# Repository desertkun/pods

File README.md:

# pods

Compact game console on `STM32F103RC6` chip with network module `NRF24L01` and `SH1106` display designed to be made as a pair.

To compile this, you'll need to install the [System Workbench for STM32](http://www.openstm32.org/Downloading%2Bthe%2BSystem%2BWorkbench%2Bfor%2BSTM32%2Binstaller) (requires an account to download).

The `layout` folder contains KiCad project for [schematics](https://user-images.githubusercontent.com/1666014/50406018-09bfe200-07c6-11e9-8298-aad8884d8a90.png).

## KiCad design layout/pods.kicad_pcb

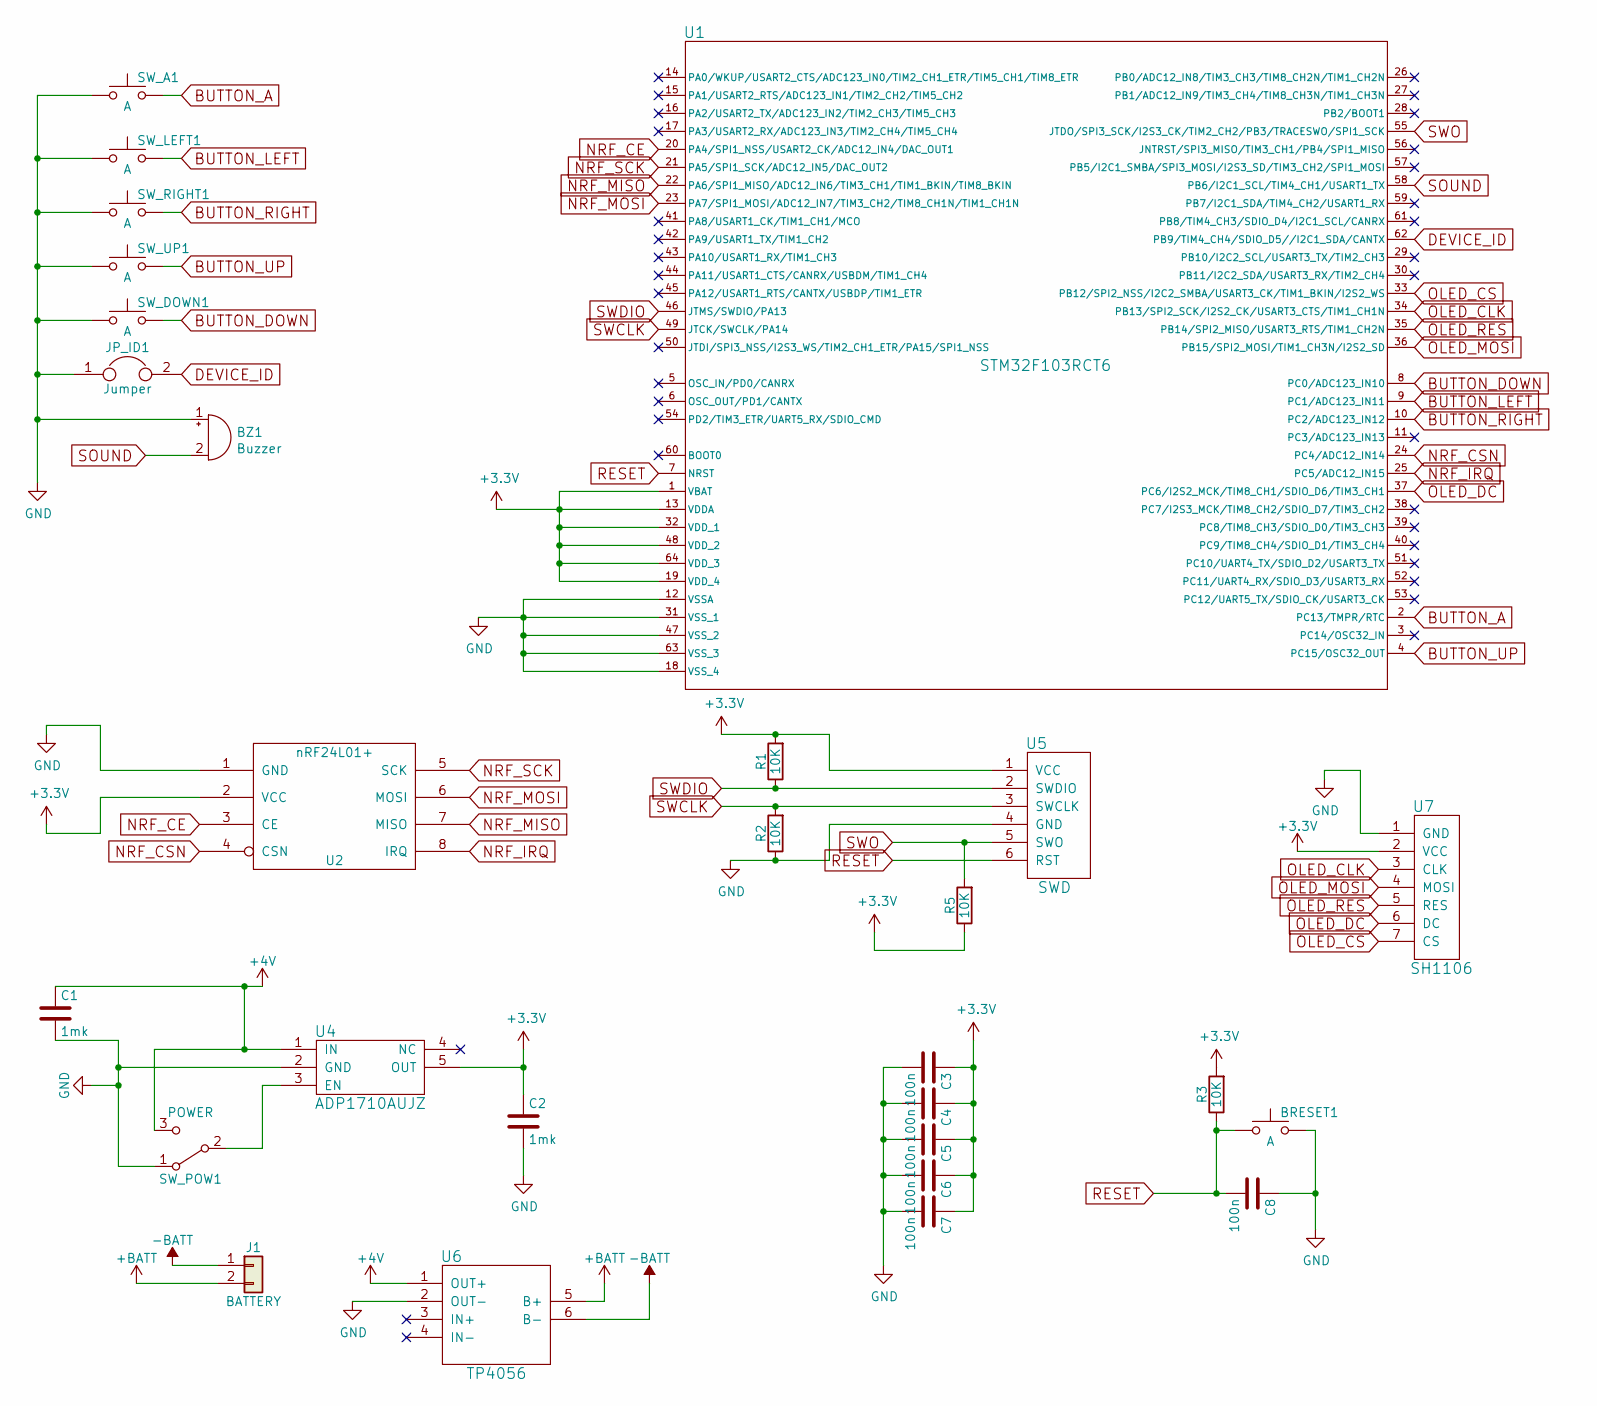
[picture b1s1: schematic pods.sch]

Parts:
BRESET1: A; SW_TH_Tactile_Omron_Fixed
BZ1: Buzzer; SolderWirePad_1x02_P3.81mm_Drill0.8mm
C1, C2: 1mk; C_0805_2012Metric_Pad1.15x1.40mm_HandSolder
C3, C4, C5, C6, C7, C8: 100n; C_0805_2012Metric_Pad1.15x1.40mm_HandSolder
J1: BATTERY; SolderWirePad_1x02_P3.81mm_Drill0.8mm
JP_ID1: Jumper; SolderWirePad_1x02_P3.81mm_Drill0.8mm
R1, R2, R3, R5: 10K; R_0805_2012Metric_Pad1.15x1.40mm_HandSolder
SW_A1: A; SW_TH_Tactile_Omron_Fixed
SW_DOWN1: A; SW_TH_Tactile_Omron_Fixed
SW_LEFT1: A; SW_TH_Tactile_Omron_Fixed
SW_POW1: POWER; SolderWirePad_1x03_P3.175mm_Drill0.8mm
SW_RIGHT1: A; SW_TH_Tactile_Omron_Fixed
SW_UP1: A; SW_TH_Tactile_Omron_Fixed
U1: STM32F103RCT6; LQFP-64_10x10mm_Pitch0.5mm
U2: nRF24L01+; NRF24L01
U4: ADP1710AUJZ; SOT-23-5_HandSoldering
U5: SWD; PinHeader_2x03_P2.54mm_Horizontal
U6: TP4056; tp4056
U7: SH1106; sh1106

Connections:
+3V3: C2.1, C3.1, C4.1, C5.1, C6.1, C7.1, R1.2, R3.2, R5.1, U1.1 (VBAT), U1.13 (VDDA), U1.19 (VDD_4), U1.32 (VDD_1), U1.48 (VDD_2), U1.64 (VDD_3), U2.2 (VCC), U4.5 (OUT), U5.1 (VCC), U7.2 (VCC)
+4V: C1.1, SW_POW1.3 (C), U4.1 (IN), U6.1 (OUT+)
+BATT: J1.2, U6.5 (B+)
-BATT: J1.1, U6.6 (B-)
BUTTON_A: SW_A1.2, U1.2 (PC13/TMPR/RTC)
BUTTON_DOWN: SW_DOWN1.2, U1.8 (PC0/ADC123_IN10)
BUTTON_LEFT: SW_LEFT1.2, U1.9 (PC1/ADC123_IN11)
BUTTON_RIGHT: SW_RIGHT1.2, U1.10 (PC2/ADC123_IN12)
BUTTON_UP: SW_UP1.2, U1.4 (PC15/OSC32_OUT)
DEVICE_ID: JP_ID1.2, U1.62 (PB9/TIM4_CH4/SDIO_D5//I2C1_SDA/CANTX)
GND: BRESET1.2, BZ1.1 (-), C1.2, C2.2, C3.2, C4.2, C5.2, C6.2, C7.2, C8.1, JP_ID1.1, R2.1, SW_A1.1, SW_DOWN1.1, SW_LEFT1.1, SW_POW1.1 (A), SW_RIGHT1.1, SW_UP1.1, U1.12 (VSSA), U1.18 (VSS_4), U1.31 (VSS_1), U1.47 (VSS_2), U1.63 (VSS_3), U2.1 (GND), U4.2 (GND), U5.4 (GND), U6.2 (OUT-), U7.1 (GND)
NRF_CE: U1.20 (PA4/SPI1_NSS/USART2_CK/ADC12_IN4/DAC_OU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), U2.3 (CE)
NRF_CSN: U1.24 (PC4/ADC12_IN14), U2.4 (CSN)
NRF_IRQ: U1.25 (PC5/ADC12_IN15), U2.8 (IRQ)
NRF_MISO: U1.22 (PA6/SPI1_MISO/ADC12_IN6/TIM3_CH1/TIM1_B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), U2.7 (MISO)
NRF_MOSI: U1.23 (PA7/SPI1_MOSI/ADC12_IN7/TIM3_CH2/TIM8_C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), U2.6 (MOSI)
NRF_SCK: U1.21 (PA5/SPI1_SCK/ADC12_IN5/DAC_OUT2), U2.5 (SCK)
unnamed: SW_POW1.2 (B), U4.3 (EN)
OLED_CLK: U1.34 (PB13/SPI2_SCK/I2S2_CK/USART3_CTS/TIM1_C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), U7.3 (CLK)
OLED_CS: U1.33 (PB12/SPI2_NSS/I2C2_SMBA/USART3_CK/TIM1_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), U7.7 (CS)
OLED_DC: U1.37 (PC6/I2S2_MCK/TIM8_CH1/SDIO_D6/TIM3_CH1), U7.6 (DC)
OLED_MOSI: U1.36 (PB15/SPI2_MOSI/TIM1_CH3N/I2S2_SD), U7.4 (MOSI)
OLED_RES: U1.35 (PB14/SPI2_MISO/USART3_RTS/TIM1_CH2N), U7.5 (RES)
RESET: BRESET1.1, C8.2, R3.1, U1.7 (NRST), U5.6 (RST)
SOUND: BZ1.2 (+), U1.58 (PB6/I2C1_SCL/TIM4_CH1/USART1_TX)
SWCLK: R2.2, U1.49 (JTCK/SWCLK/PA14), U5.3 (SWCLK)
SWDIO: R1.1, U1.46 (JTMS/SWDIO/PA13), U5.2 (SWDIO)
SWO: R5.2, U1.55 (JTDO/SPI3_SCK/I2S3_CK/TIM2_CH2/PB3/TRAC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), U5.5 (SWO)

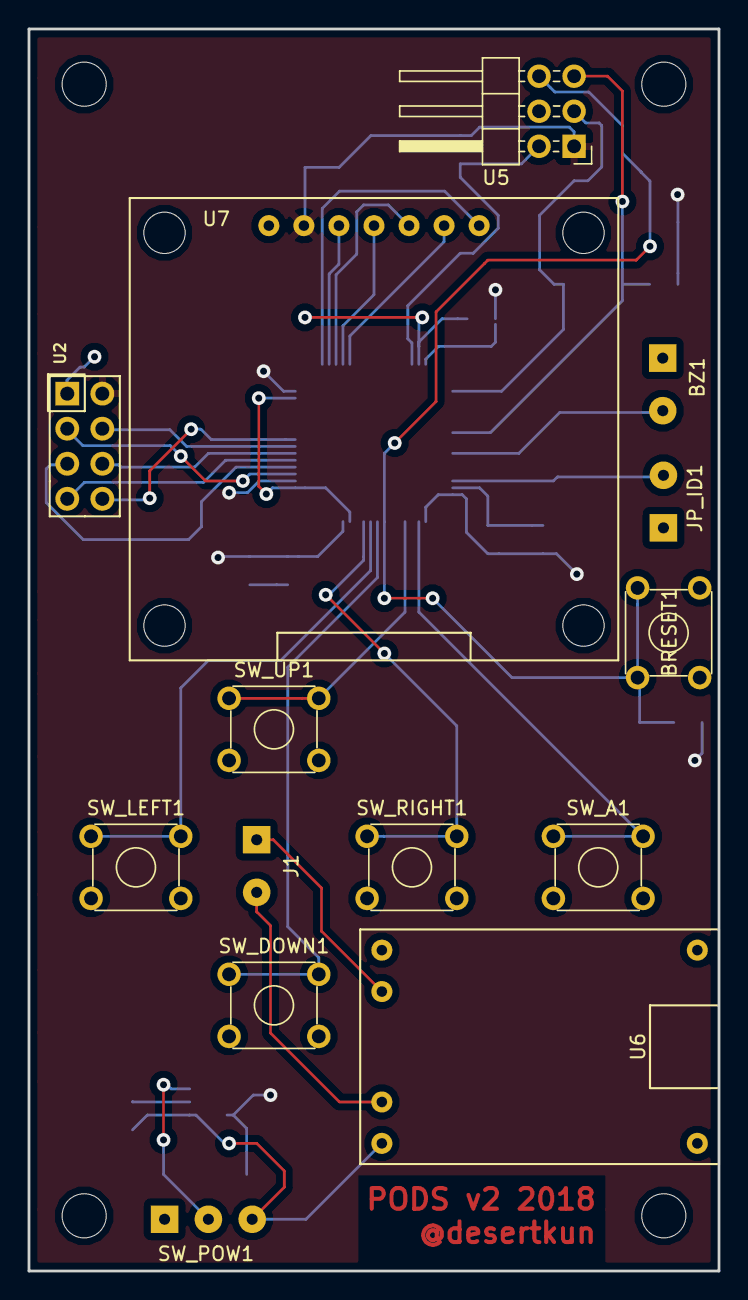
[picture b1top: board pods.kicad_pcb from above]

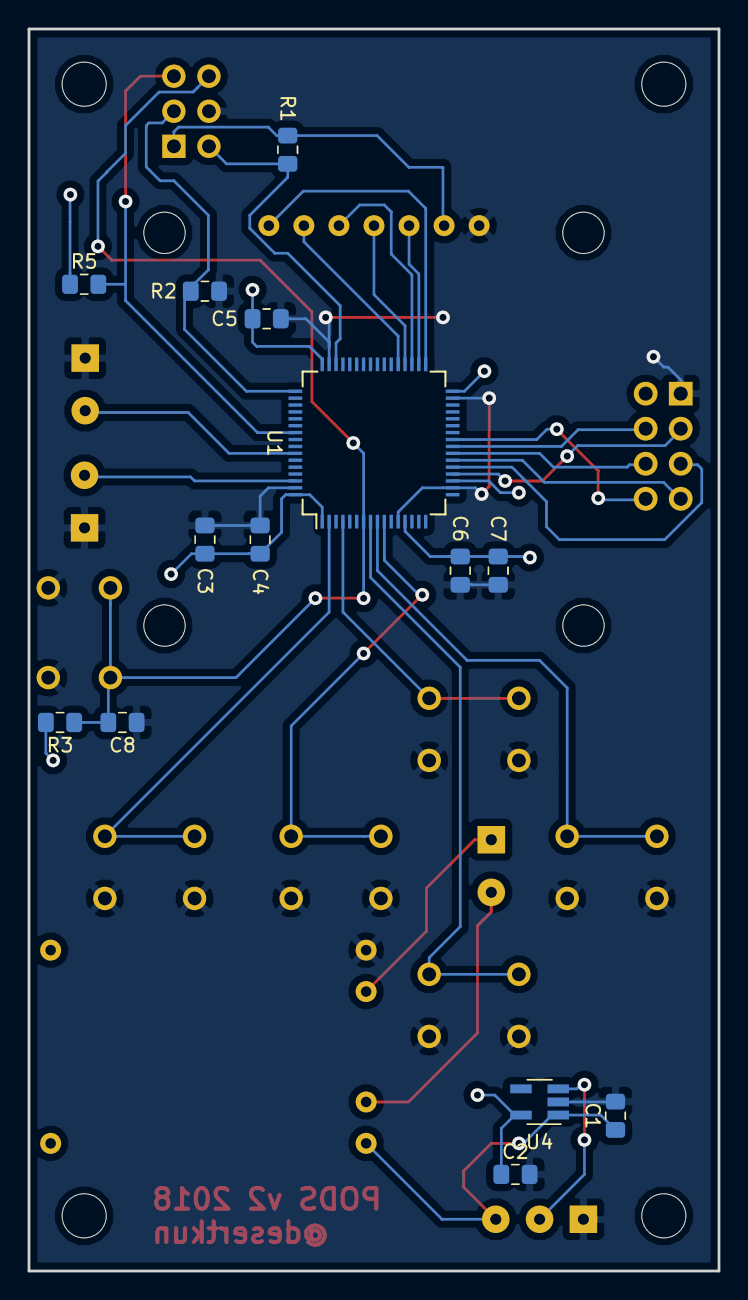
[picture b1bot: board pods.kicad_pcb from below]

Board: 2 copper layers, 50.0 x 90.0 mm, 28 parts (14 on the bottom side), 28 nets.

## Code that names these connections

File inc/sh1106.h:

#ifndef __SH1106_H
#define __SH1106_H

#include "stm32f1xx_hal.h"
#include "main.h"

// SH1106 display connection:
//   PB8 --> CS
//   PB9 --> RES
//   PC0 --> DC
//   PA5 --> D0 (SCK)
//   PA7 --> D1 (MOSI)


// Use bit-banding to draw pixel
//   0 - use logic operations to set pixel color
//   1 - use bit-banding to set pixel color
#define SH1106_USE_BITBAND   1

// Pixel set function definition
//   0 - call pixel function (less code size in cost of speed)
//   1 - inline pixel function (higher speed in cost of code size)
#define SH1106_OPT_PIXEL     1

// DMA usage
//   0 - DMA is not used
//   1 - compile functions for DMA transfer VRAM to display
#define SH1106_USE_DMA       0


// SH1106 HAL

// SPI port
#define SH1106_SPI_PORT      hspi2

// GPIO peripherals
#define SH1106_GPIO_PERIPH   (RCC_AHBENR_GPIOBEN | RCC_AHBENR_GPIOCEN)

// SH1106 RS/A0 (Data/Command select) pin (PC6)
#define SH1106_DC_PORT       GPIOC
#define SH1106_DC_PIN        GPIO_PIN_6
#define SH1106_DC_H()        HAL_GPIO_WritePin(SH1106_DC_PORT, SH1106_DC_PIN,GPIO_PIN_SET)
#define SH1106_DC_L()        HAL_GPIO_WritePin(SH1106_DC_PORT, SH1106_DC_PIN,GPIO_PIN_RESET)

// SH1106 RST (Reset) pin (PB14)
#define SH1106_RST_PORT      GPIOB
#define SH1106_RST_PIN       GPIO_PIN_14
#define SH1106_RST_H()       HAL_GPIO_WritePin(SH1106_RST_PORT, SH1106_RST_PIN,GPIO_PIN_SET)
#define SH1106_RST_L()       HAL_GPIO_WritePin(SH1106_RST_PORT, SH1106_RST_PIN,GPIO_PIN_RESET)

// SH1106 CS (Chip Select) pin (PB12)
#define SH1106_CS_PORT       GPIOB
#define SH1106_CS_PIN        GPIO_PIN_12
#define SH1106_CS_H()        HAL_GPIO_WritePin(SH1106_CS_PORT, SH1106_CS_PIN,GPIO_PIN_SET)
#define SH1106_CS_L()        HAL_GPIO_WritePin(SH1106_CS_PORT, SH1106_CS_PIN,GPIO_PIN_RESET)


// Screen dimensions
#define SCR_W                 (uint8_t)128 // width
#define SCR_H                 (uint8_t)64  // height


// SH1106 command definitions
#define SH1106_CMD_SETMUX    (uint8_t)0xA8 // Set multiplex ratio (N, number of lines active on display)
#define SH1106_CMD_SETOFFS   (uint8_t)0xD3 // Set display offset
#define SH1106_CMD_STARTLINE (uint8_t)0x40 // Set display start line
#define SH1106_CMD_SEG_NORM  (uint8_t)0xA0 // Column 0 is mapped to SEG0 (X coordinate normal)
#define SH1106_CMD_SEG_INV   (uint8_t)0xA1 // Column 127 is mapped to SEG0 (X coordinate inverted)
#define SH1106_CMD_COM_NORM  (uint8_t)0xC0 // Scan from COM0 to COM[N-1] (N - mux ratio, Y coordinate normal)
#define SH1106_CMD_COM_INV   (uint8_t)0xC8 // Scan from COM[N-1] to COM0 (N - mux ratio, Y coordinate inverted)
#define SH1106_CMD_COM_HW    (uint8_t)0xDA // Set COM pins hardware configuration
#define SH1106_CMD_CONTRAST  (uint8_t)0x81 // Contrast control
#define SH1106_CMD_EDON      (uint8_t)0xA5 // Entire display ON enabled (all pixels on, RAM content ignored)
#define SH1106_CMD_EDOFF     (uint8_t)0xA4 // Entire display ON disabled (output follows RAM content)
#define SH1106_CMD_INV_OFF   (uint8_t)0xA6 // Entire display inversion OFF (normal display)
#define SH1106_CMD_INV_ON    (uint8_t)0xA7 // Entire display inversion ON (all pixels inverted)
#define SH1106_CMD_CLOCKDIV  (uint8_t)0xD5 // Set display clock divide ratio/oscillator frequency
#define SH1106_CMD_DISP_ON   (uint8_t)0xAF // Display ON
#define SH1106_CMD_DISP_OFF  (uint8_t)0xAE // Display OFF (sleep mode)

#define SH1106_CMD_COL_LOW   (uint8_t)0x00 // Set Lower Column Address
#define SH1106_CMD_COL_HIGH  (uint8_t)0x10 // Set Higher Column Address
#define SH1106_CMD_PAGE_ADDR (uint8_t)0xB0 // Set Page Address

#define SH1106_CMD_VCOMH     (uint8_t)0xDB // Set Vcomh deselect level
#define SH1106_CMD_SCRL_HR   (uint8_t)0x26 // Setup continuous horizontal scroll right
#define SH1106_CMD_SCRL_HL   (uint8_t)0x27 // Setup continuous horizontal scroll left
#define SH1106_CMD_SCRL_VHR  (uint8_t)0x29 // Setup continuous vertical and horizontal scroll right
#define SH1106_CMD_SCRL_VHL  (uint8_t)0x2A // Setup continuous vertical and horizontal scroll left
#define SH1106_CMD_SCRL_STOP (uint8_t)0x2E // Deactivate scroll
#define SH1106_CMD_SCRL_ACT  (uint8_t)0x2F // Activate scroll


// Entire display on/off enumeration
enum {
	LCD_ENTIRE_PIXELS_OFF = 0,
	LCD_ENTIRE_PIXELS_ON  = !LCD_ENTIRE_PIXELS_OFF
};

// Display pixels inversion enumeration
enum {
	LCD_INVERT_OFF = 0,
	LCD_INVERT_ON  = !LCD_INVERT_OFF
};

// Display ON/OFF enumeration
enum {
	LCD_OFF = 0,
	LCD_ON  = !LCD_OFF
};

// Screen orientation enumeration
enum {
	LCD_ORIENT_NORMAL = 0, // No rotation
	LCD_ORIENT_CW     = 1, // Clockwise rotation
	LCD_ORIENT_CCW    = 2, // Counter-clockwise rotation
	LCD_ORIENT_180    = 3  // 180 degrees rotation
};

// Screen horizontal scroll direction enumeration
enum {
	LCD_SCROLL_RIGHT = 0, // Scroll right
	LCD_SCROLL_LEFT  = 1  // Scroll left
};

// Screen scroll interval enumeration
enum {
	LCD_SCROLL_IF2   = 0x07, // 2 frames
	LCD_SCROLL_IF3   = 0x04, // 3 frames
	LCD_SCROLL_IF4   = 0x05, // 4 frames
	LCD_SCROLL_IF5   = 0x00, // 5 frames
	LCD_SCROLL_IF25  = 0x06, // 25 frames
	LCD_SCROLL_IF64  = 0x01, // 64 frames
	LCD_SCROLL_IF128 = 0x02, // 128 frames
	LCD_SCROLL_IF256 = 0x03  // 256 frames
};

// Pixel draw mode
enum {
	LCD_PSET = 0x00, // Set pixel
	LCD_PRES = 0x01, // Reset pixel
	LCD_PINV = 0x02  // Invert pixel
};

// Font structure scan lines enumeration
enum {
	FONT_V = (uint8_t)0,        // Vertical font scan lines
	FONT_H = (uint8_t)(!FONT_V) // Horizontal font scan lines
};


// Font descriptor
typedef struct {
	uint8_t font_Width;       // Width of character
	uint8_t font_Height;      // Height of character
	uint8_t font_BPC;         // Bytes for one character
	uint8_t font_Scan;        // Font scan lines behavior
	uint8_t font_MinChar;     // Code of the first known symbol
	uint8_t font_MaxChar;     // Code of the last known symbol
	uint8_t font_UnknownChar; // Code of the unknown symbol
	uint8_t font_Data[];      // Font data
} Font_TypeDef;


// Public variables
extern uint16_t scr_width;
extern uint16_t scr_height;
extern uint8_t LCD_PixelMode;

extern SPI_HandleTypeDef SH1106_SPI_PORT;

// Function prototypes
//void SH1106_InitGPIO(void);
void SH1106_Init(void);

void SH1106_Contrast(uint8_t contrast);
void SH1106_SetAllPixelsOn(uint8_t eon_state);
void SH1106_SetInvert(uint8_t inv_state);
void SH1106_SetDisplayState(uint8_t disp_state);
void SH1106_SetXDir(uint8_t x_map);
void SH1106_SetYDir(uint8_t y_map);
void SH1106_Orientation(uint8_t orientation);

void SH1106_Flush(void);
#if (SH1106_USE_DMA)
void SH1106_Flush_DMA(void);
#endif // SH1106_USE_DMA

void SH1106_Fill(uint8_t pattern);

void SH1106_ScrollHSetup(uint8_t dir, uint8_t start, uint8_t end, uint8_t interval);
void SH1106_ScrollDSetup(uint8_t dir, uint8_t start, uint8_t end, uint8_t interval, uint8_t voffs);
void SH1106_ScrollStart(void);
void SH1106_ScrollStop(void);

#if (SH1106_OPT_PIXEL)
inline void LCD_Pixel(uint8_t X, uint8_t Y, uint8_t Mode);
#else
void LCD_Pixel(uint8_t X, uint8_t Y, uint8_t Mode);
#endif // SH1106_OPT_PIXEL

void LCD_HLine(uint8_t X1, uint8_t X2, uint8_t Y);
void LCD_VLine(uint8_t X, uint8_t Y1, uint8_t Y2);
void LCD_Rect(uint8_t X1, uint8_t Y1, uint8_t X2, uint8_t Y2);
void LCD_FillRect(uint8_t X1, uint8_t Y1, uint8_t X2, uint8_t Y2);
void LCD_Line(int16_t X1, int16_t Y1, int16_t X2, int16_t Y2);
void LCD_Circle(int16_t X, int16_t Y, uint8_t R);
void LCD_Ellipse(uint16_t Xc, uint16_t Yc, uint16_t Ra, uint16_t Rb);

uint8_t LCD_PutChar(uint8_t X, uint8_t Y, uint8_t Char, const Font_TypeDef *Font);
uint16_t LCD_PutStr(uint8_t X, uint8_t Y, const char *str, const Font_TypeDef *Font);
uint16_t LCD_PutStrLF(uint8_t X, uint8_t Y, const char *str, const Font_TypeDef *Font);
uint8_t LCD_PutInt(uint8_t X, uint8_t Y, int32_t num, const Font_TypeDef *Font);
uint8_t LCD_PutIntU(uint8_t X, uint8_t Y, uint32_t num, const Font_TypeDef *Font);
uint8_t LCD_PutIntF(uint8_t X, uint8_t Y, int32_t num, uint8_t decimals, const Font_TypeDef *Font);
uint8_t LCD_PutIntLZ(uint8_t X, uint8_t Y, int32_t num, uint8_t digits, const Font_TypeDef *Font);
uint8_t LCD_PutHex(uint8_t X, uint8_t Y, uint32_t num, const Font_TypeDef *Font);

void LCD_DrawBitmap(uint8_t X, uint8_t Y, uint8_t W, uint8_t H, const uint8_t* pBMP);

#endif // __SH1106_H

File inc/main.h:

/**
  ******************************************************************************
  * @file           : main.h
  * @brief          : Header for main.c file.
  *                   This file contains the common defines of the application.
  ******************************************************************************
  ** This notice applies to any and all portions of this file
  * that are not between comment pairs USER CODE BEGIN and
  * USER CODE END. Other portions of this file, whether 
  * inserted by the user or by software development tools
  * are owned by their respective copyright owners.
  *
  * COPYRIGHT(c) 2018 STMicroelectronics
  *
  * Redistribution and use in source and binary forms, with or without modification,
  * are permitted provided that the following conditions are met:
  *   1. Redistributions of source code must retain the above copyright notice,
  *      this list of conditions and the following disclaimer.
  *   2. Redistributions in binary form must reproduce the above copyright notice,
  *      this list of conditions and the following disclaimer in the documentation
  *      and/or other materials provided with the distribution.
  *   3. Neither the name of STMicroelectronics nor the names of its contributors
  *      may be used to endorse or promote products derived from this software
  *      without specific prior written permission.
  *
  * THIS SOFTWARE IS PROVIDED BY THE COPYRIGHT HOLDERS AND CONTRIBUTORS "AS IS"
  * AND ANY EXPRESS OR IMPLIED WARRANTIES, INCLUDING, BUT NOT LIMITED TO, THE
  * IMPLIED WARRANTIES OF MERCHANTABILITY AND FITNESS FOR A PARTICULAR PURPOSE ARE
  * DISCLAIMED. IN NO EVENT SHALL THE COPYRIGHT HOLDER OR CONTRIBUTORS BE LIABLE
  * FOR ANY DIRECT, INDIRECT, INCIDENTAL, SPECIAL, EXEMPLARY, OR CONSEQUENTIAL
  * DAMAGES (INCLUDING, BUT NOT LIMITED TO, PROCUREMENT OF SUBSTITUTE GOODS OR
  * SERVICES; LOSS OF USE, DATA, OR PROFITS; OR BUSINESS INTERRUPTION) HOWEVER
  * CAUSED AND ON ANY THEORY OF LIABILITY, WHETHER IN CONTRACT, STRICT LIABILITY,
  * OR TORT (INCLUDING NEGLIGENCE OR OTHERWISE) ARISING IN ANY WAY OUT OF THE USE
  * OF THIS SOFTWARE, EVEN IF ADVISED OF THE POSSIBILITY OF SUCH DAMAGE.
  *
  ******************************************************************************
  */

/* Define to prevent recursive inclusion -------------------------------------*/
#ifndef __MAIN_H__
#define __MAIN_H__

/* Includes ------------------------------------------------------------------*/

/* USER CODE BEGIN Includes */

/* USER CODE END Includes */

/* Private define ------------------------------------------------------------*/

#define CTL_A_Pin GPIO_PIN_13
#define CTL_A_GPIO_Port GPIOC
#define CTL_UP_Pin GPIO_PIN_15
#define CTL_UP_GPIO_Port GPIOC
#define CTL_DOWN_Pin GPIO_PIN_0
#define CTL_DOWN_GPIO_Port GPIOC
#define CTL_LEFT_Pin GPIO_PIN_1
#define CTL_LEFT_GPIO_Port GPIOC
#define CTL_RIGHT_Pin GPIO_PIN_2
#define CTL_RIGHT_GPIO_Port GPIOC
#define NRF_CE_Pin GPIO_PIN_4
#define NRF_CE_GPIO_Port GPIOA
#define NRF_CS_Pin GPIO_PIN_4
#define NRF_CS_GPIO_Port GPIOC
#define NRF_IRQ_Pin GPIO_PIN_5
#define NRF_IRQ_GPIO_Port GPIOC
#define NRF_IRQ_EXTI_IRQn EXTI9_5_IRQn
#define OLED_CS_Pin GPIO_PIN_12
#define OLED_CS_GPIO_Port GPIOB
#define OLED_RES_Pin GPIO_PIN_14
#define OLED_RES_GPIO_Port GPIOB
#define OLED_DC_Pin GPIO_PIN_6
#define OLED_DC_GPIO_Port GPIOC
#define BUZZER_Pin GPIO_PIN_6
#define BUZZER_GPIO_Port GPIOB
#define DEVICE_ID_Pin GPIO_PIN_9
#define DEVICE_ID_GPIO_Port GPIOB

/* ########################## Assert Selection ############################## */
/**
  * @brief Uncomment the line below to expanse the "assert_param" macro in the 
  *        HAL drivers code
  */
/* #define USE_FULL_ASSERT    1U */

/* USER CODE BEGIN Private defines */

/* USER CODE END Private defines */

#ifdef __cplusplus
 extern "C" {
#endif
void _Error_Handler(char *, int);

#define Error_Handler() _Error_Handler(__FILE__, __LINE__)
#ifdef __cplusplus
}
#endif

#endif /* __MAIN_H__ */

/************************ (C) COPYRIGHT STMicroelectronics *****END OF FILE****/

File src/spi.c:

/**
  ******************************************************************************
  * File Name          : SPI.c
  * Description        : This file provides code for the configuration
  *                      of the SPI instances.
  ******************************************************************************
  ** This notice applies to any and all portions of this file
  * that are not between comment pairs USER CODE BEGIN and
  * USER CODE END. Other portions of this file, whether 
  * inserted by the user or by software development tools
  * are owned by their respective copyright owners.
  *
  * COPYRIGHT(c) 2018 STMicroelectronics
  *
  * Redistribution and use in source and binary forms, with or without modification,
  * are permitted provided that the following conditions are met:
  *   1. Redistributions of source code must retain the above copyright notice,
  *      this list of conditions and the following disclaimer.
  *   2. Redistributions in binary form must reproduce the above copyright notice,
  *      this list of conditions and the following disclaimer in the documentation
  *      and/or other materials provided with the distribution.
  *   3. Neither the name of STMicroelectronics nor the names of its contributors
  *      may be used to endorse or promote products derived from this software
  *      without specific prior written permission.
  *
  * THIS SOFTWARE IS PROVIDED BY THE COPYRIGHT HOLDERS AND CONTRIBUTORS "AS IS"
  * AND ANY EXPRESS OR IMPLIED WARRANTIES, INCLUDING, BUT NOT LIMITED TO, THE
  * IMPLIED WARRANTIES OF MERCHANTABILITY AND FITNESS FOR A PARTICULAR PURPOSE ARE
  * DISCLAIMED. IN NO EVENT SHALL THE COPYRIGHT HOLDER OR CONTRIBUTORS BE LIABLE
  * FOR ANY DIRECT, INDIRECT, INCIDENTAL, SPECIAL, EXEMPLARY, OR CONSEQUENTIAL
  * DAMAGES (INCLUDING, BUT NOT LIMITED TO, PROCUREMENT OF SUBSTITUTE GOODS OR
  * SERVICES; LOSS OF USE, DATA, OR PROFITS; OR BUSINESS INTERRUPTION) HOWEVER
  * CAUSED AND ON ANY THEORY OF LIABILITY, WHETHER IN CONTRACT, STRICT LIABILITY,
  * OR TORT (INCLUDING NEGLIGENCE OR OTHERWISE) ARISING IN ANY WAY OUT OF THE USE
  * OF THIS SOFTWARE, EVEN IF ADVISED OF THE POSSIBILITY OF SUCH DAMAGE.
  *
  ******************************************************************************
  */

/* Includes ------------------------------------------------------------------*/
#include "spi.h"

#include "gpio.h"

/* USER CODE BEGIN 0 */

/* USER CODE END 0 */

SPI_HandleTypeDef hspi1;
SPI_HandleTypeDef hspi2;

/* SPI1 init function */
void MX_SPI1_Init(void)
{

  hspi1.Instance = SPI1;
  hspi1.Init.Mode = SPI_MODE_MASTER;
  hspi1.Init.Direction = SPI_DIRECTION_2LINES;
  hspi1.Init.DataSize = SPI_DATASIZE_8BIT;
  hspi1.Init.CLKPolarity = SPI_POLARITY_LOW;
  hspi1.Init.CLKPhase = SPI_PHASE_1EDGE;
  hspi1.Init.NSS = SPI_NSS_SOFT;
  hspi1.Init.BaudRatePrescaler = SPI_BAUDRATEPRESCALER_2;
  hspi1.Init.FirstBit = SPI_FIRSTBIT_MSB;
  hspi1.Init.TIMode = SPI_TIMODE_DISABLE;
  hspi1.Init.CRCCalculation = SPI_CRCCALCULATION_DISABLE;
  hspi1.Init.CRCPolynomial = 10;
  if (HAL_SPI_Init(&hspi1) != HAL_OK)
  {
    _Error_Handler(__FILE__, __LINE__);
  }

}
/* SPI2 init function */
void MX_SPI2_Init(void)
{

  hspi2.Instance = SPI2;
  hspi2.Init.Mode = SPI_MODE_MASTER;
  hspi2.Init.Direction = SPI_DIRECTION_1LINE;
  hspi2.Init.DataSize = SPI_DATASIZE_8BIT;
  hspi2.Init.CLKPolarity = SPI_POLARITY_LOW;
  hspi2.Init.CLKPhase = SPI_PHASE_1EDGE;
  hspi2.Init.NSS = SPI_NSS_SOFT;
  hspi2.Init.BaudRatePrescaler = SPI_BAUDRATEPRESCALER_2;
  hspi2.Init.FirstBit = SPI_FIRSTBIT_MSB;
  hspi2.Init.TIMode = SPI_TIMODE_DISABLE;
  hspi2.Init.CRCCalculation = SPI_CRCCALCULATION_DISABLE;
  hspi2.Init.CRCPolynomial = 10;
  if (HAL_SPI_Init(&hspi2) != HAL_OK)
  {
    _Error_Handler(__FILE__, __LINE__);
  }

}

void HAL_SPI_MspInit(SPI_HandleTypeDef* spiHandle)
{

  GPIO_InitTypeDef GPIO_InitStruct;
  if(spiHandle->Instance==SPI1)
  {
  /* USER CODE BEGIN SPI1_MspInit 0 */

  /* USER CODE END SPI1_MspInit 0 */
    /* SPI1 clock enable */
    __HAL_RCC_SPI1_CLK_ENABLE();
  
    /**SPI1 GPIO Configuration    
    PA5     ------> SPI1_SCK
    PA6     ------> SPI1_MISO
    PA7     ------> SPI1_MOSI 
    */
    GPIO_InitStruct.Pin = GPIO_PIN_5|GPIO_PIN_7;
    GPIO_InitStruct.Mode = GPIO_MODE_AF_PP;
    GPIO_InitStruct.Speed = GPIO_SPEED_FREQ_HIGH;
    HAL_GPIO_Init(GPIOA, &GPIO_InitStruct);

    GPIO_InitStruct.Pin = GPIO_PIN_6;
    GPIO_InitStruct.Mode = GPIO_MODE_INPUT;
    GPIO_InitStruct.Pull = GPIO_NOPULL;
    HAL_GPIO_Init(GPIOA, &GPIO_InitStruct);

  /* USER CODE BEGIN SPI1_MspInit 1 */

  /* USER CODE END SPI1_MspInit 1 */
  }
  else if(spiHandle->Instance==SPI2)
  {
  /* USER CODE BEGIN SPI2_MspInit 0 */

  /* USER CODE END SPI2_MspInit 0 */
    /* SPI2 clock enable */
    __HAL_RCC_SPI2_CLK_ENABLE();
  
    /**SPI2 GPIO Configuration    
    PB13     ------> SPI2_SCK
    PB15     ------> SPI2_MOSI 
    */
    GPIO_InitStruct.Pin = GPIO_PIN_13|GPIO_PIN_15;
    GPIO_InitStruct.Mode = GPIO_MODE_AF_PP;
    GPIO_InitStruct.Speed = GPIO_SPEED_FREQ_HIGH;
    HAL_GPIO_Init(GPIOB, &GPIO_InitStruct);

  /* USER CODE BEGIN SPI2_MspInit 1 */

  /* USER CODE END SPI2_MspInit 1 */
  }
}

void HAL_SPI_MspDeInit(SPI_HandleTypeDef* spiHandle)
{

  if(spiHandle->Instance==SPI1)
  {
  /* USER CODE BEGIN SPI1_MspDeInit 0 */

  /* USER CODE END SPI1_MspDeInit 0 */
    /* Peripheral clock disable */
    __HAL_RCC_SPI1_CLK_DISABLE();
  
    /**SPI1 GPIO Configuration    
    PA5     ------> SPI1_SCK
    PA6     ------> SPI1_MISO
    PA7     ------> SPI1_MOSI 
    */
    HAL_GPIO_DeInit(GPIOA, GPIO_PIN_5|GPIO_PIN_6|GPIO_PIN_7);

  /* USER CODE BEGIN SPI1_MspDeInit 1 */

  /* USER CODE END SPI1_MspDeInit 1 */
  }
  else if(spiHandle->Instance==SPI2)
  {
  /* USER CODE BEGIN SPI2_MspDeInit 0 */

  /* USER CODE END SPI2_MspDeInit 0 */
    /* Peripheral clock disable */
    __HAL_RCC_SPI2_CLK_DISABLE();
  
    /**SPI2 GPIO Configuration    
    PB13     ------> SPI2_SCK
    PB15     ------> SPI2_MOSI 
    */
    HAL_GPIO_DeInit(GPIOB, GPIO_PIN_13|GPIO_PIN_15);

  /* USER CODE BEGIN SPI2_MspDeInit 1 */

  /* USER CODE END SPI2_MspDeInit 1 */
  }
} 

/* USER CODE BEGIN 1 */

/* USER CODE END 1 */

/**
  * @}
  */

/**
  * @}
  */

/************************ (C) COPYRIGHT STMicroelectronics *****END OF FILE****/

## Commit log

2018-02-25 C++ Application layout
2018-02-25 Updated layout
2018-03-10 Network working prototype
2018-11-21 Some progress
2018-11-22 Music
2018-11-24 Working prototype
    Fixed network
    Full-blown music
    Moving characters
2018-11-24 Smooth moving (32mhz)
2018-11-24 Working game loop
2018-11-25 Removed key B (do not need that one)
2018-11-29 Multiple bombs, In-game sounds
2018-11-29 New PCB design
2018-12-02 Updated kicad design
2018-12-24 Updated schematic/pcb
